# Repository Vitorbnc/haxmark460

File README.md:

# haxmark460
Direct PCB printer based on a Lexmark E460dn

[Detailed build instructions here](https://hackaday.io/project/171775-haxmark460-home-pcb-printer). 

Based on the [haxmark](https://github.com/fruchti/haxmark) project and [this instructable](https://www.instructables.com/Modification-of-the-Lexmark-E260-Laser-Printer-for/).

Quick demo video [here](https://www.youtube.com/watch?v=Cp2N5aJ5IuY).

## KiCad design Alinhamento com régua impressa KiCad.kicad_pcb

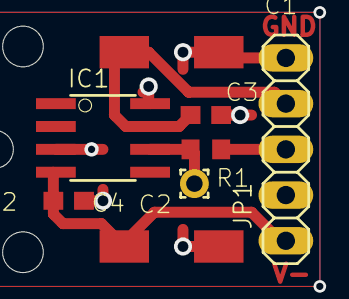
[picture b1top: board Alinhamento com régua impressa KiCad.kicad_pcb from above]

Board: 2 copper layers, 11 parts (0 on the bottom side), 5 nets.

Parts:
@HOLE0, @HOLE1, @HOLE2: (no value)
C1, C2: 4.7uF; C_6032-28W
C3, C4: 0.1uF; C0603
IC1: OPA124U; SO08
JP1: PINHD-1X5; 1X05
PAD1: 1,6_0,9
R1: 220; R0603

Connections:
+9V: C1.+, C3.1, IC1.7, JP1.2
-9V: C2.+, C4.1, IC1.4, JP1.5
GND: C1.-, C2.-, C3.2, C4.2, IC1.3, IC1.8, JP1.1, JP1.4
unnamed: IC1.6, PAD1.1, R1.1
unnamed: JP1.3, R1.2
